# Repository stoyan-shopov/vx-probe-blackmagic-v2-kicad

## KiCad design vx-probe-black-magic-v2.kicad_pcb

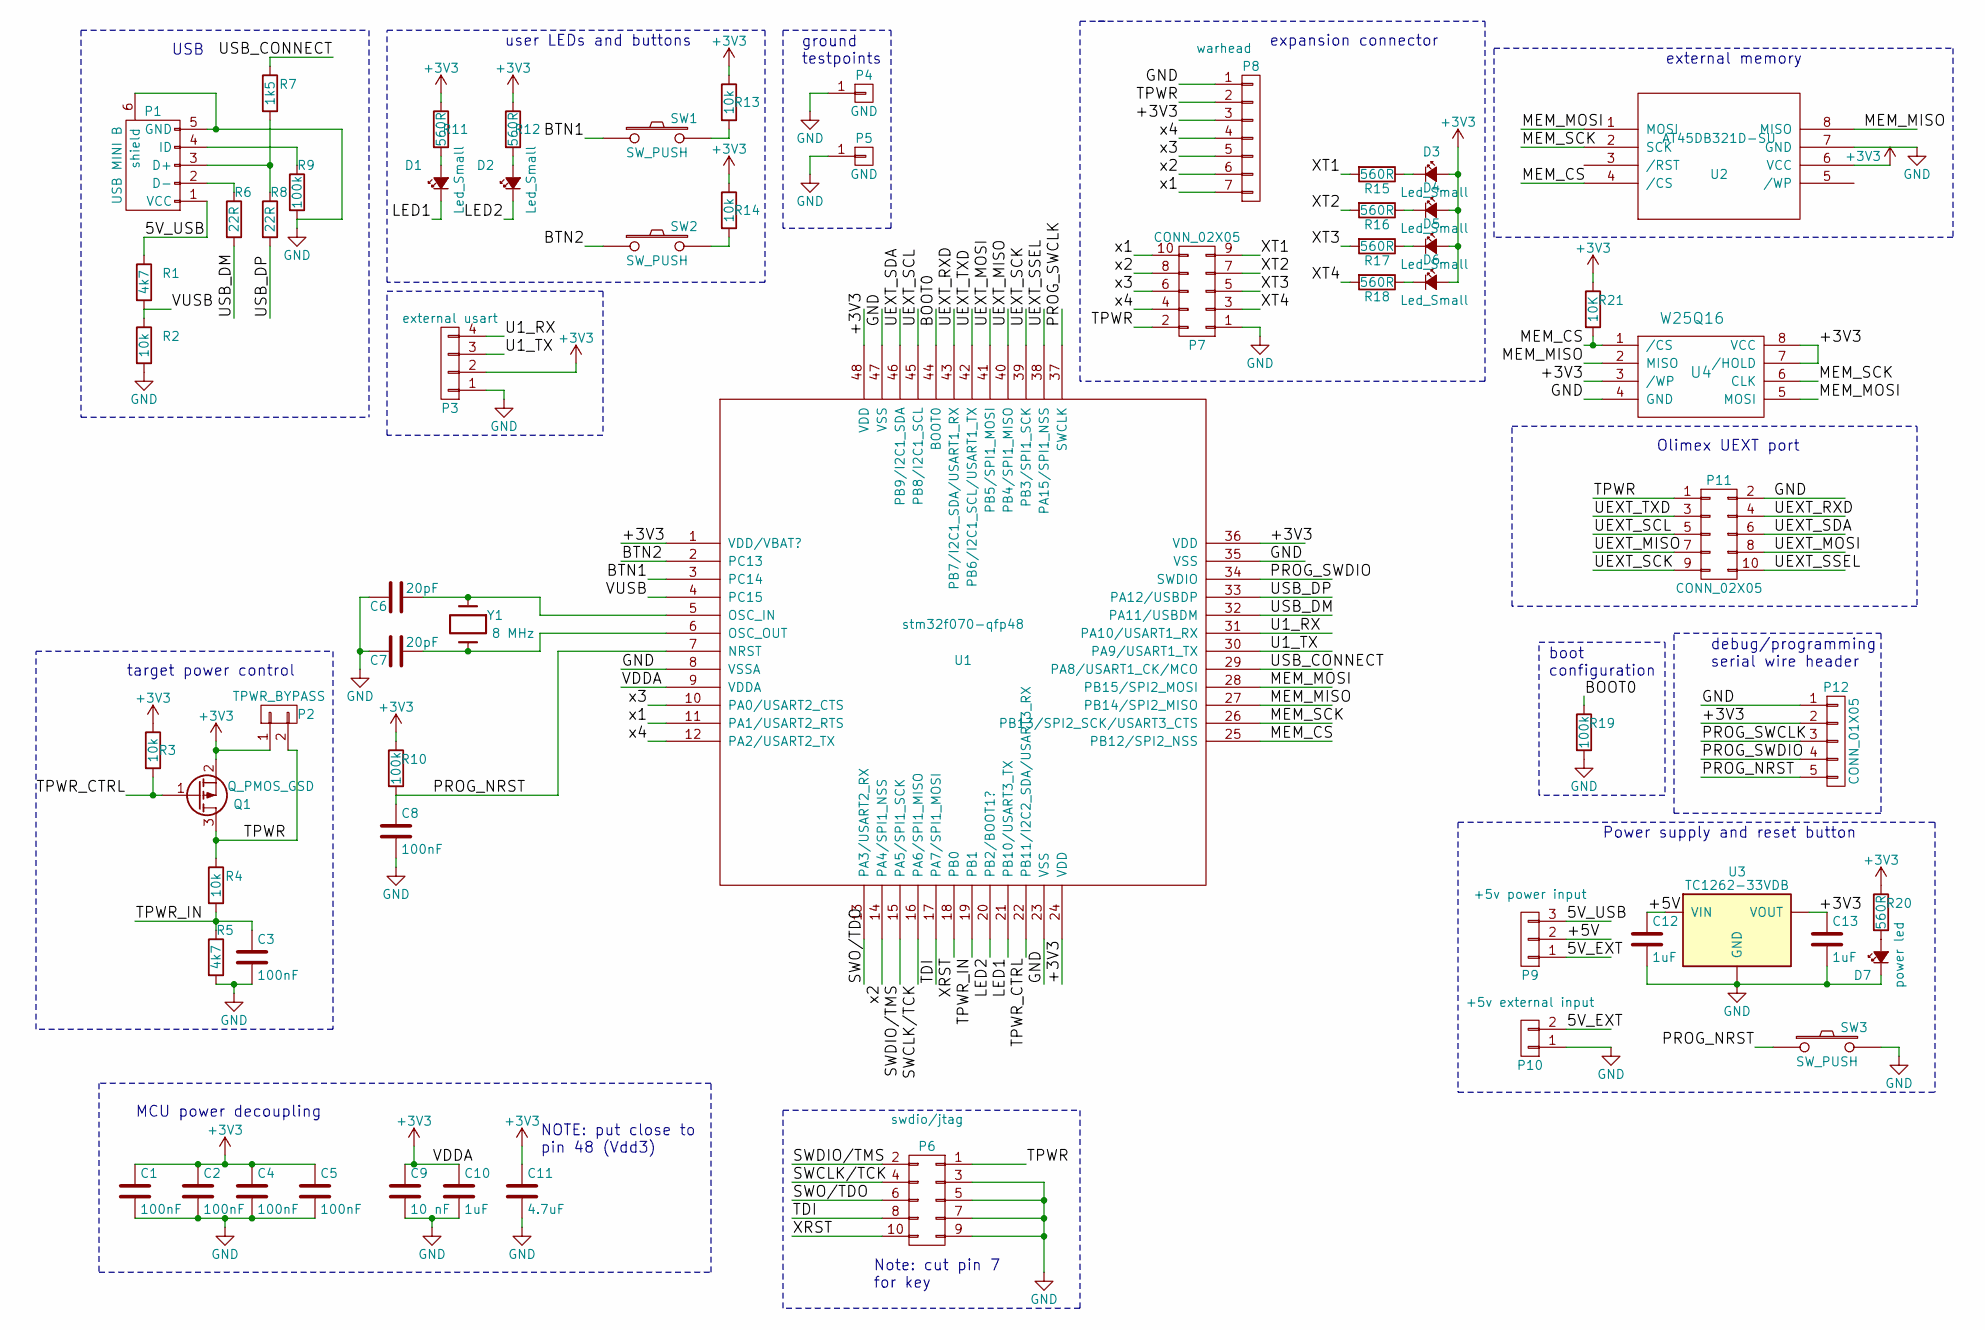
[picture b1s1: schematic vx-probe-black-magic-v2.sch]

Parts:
C1, C2, C3, C4, C5, C8: 100nF; C_0805
C6, C7: 20pF; C_0805
C9: 10 nF; C_0805
C10, C12, C13: 1uF; C_0805
C11: 4.7uF; C_0805
D1, D2, D3, D4, D5, D6: Led_Small; LED_0805
D7: power led; LED_0805
P1: USB MINI B; USB_Mini-B
P2: TPWR_BYPASS; Pin_Header_Straight_1x02
P3: external usart; Pin_Header_Straight_1x04
P4, P5: GND; Pin_Header_Straight_1x01
P6: swdio/jtag; IDC_Header_Straight_10pins
P7: CONN_02X05; Pin_Header_Straight_2x05
P8: warhead; Pin_Header_Straight_1x07
P9: +5v power input; Pin_Header_Straight_1x03
P10: +5v external input; Pin_Header_Straight_1x02
P11: CONN_02X05; IDC_Header_Straight_10pins
P12: CONN_01X05; Pin_Header_Straight_1x05
Q1: Q_PMOS_GSD; SOT-23
R1, R5: 4k7; R_0805
R2, R3, R4, R13, R14: 10k; R_0805
R6, R8: 22R; R_0805
R7: 1k5; R_0805
R9, R10, R19: 100k; R_0805
R11, R12, R15, R16, R17, R18, R20: 560R; R_0805
R21: 10K; R_0805
SW1, SW2, SW3: SW_PUSH; SW_PUSH_6mm
U1: stm32f070-qfp48; LQFP-48_7x7mm_Pitch0.5mm
U2: AT45DB321D-SU; SOIJ-8_5.3x5.3mm_Pitch1.27mm
U3: TC1262-33VDB; SOT-223
U4: W25Q16; SOIJ-8_5.3x5.3mm_Pitch1.27mm
Y1: 8 MHz; Crystal_HC49-U_Vertical

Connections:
+3V3: C1.1, C2.1, C4.1, C5.1, C9.1, C10.1, C11.1, C13.1, D3.2 (A), D4.2 (A), D5.2 (A), D6.2 (A), P2.1, P3.2, P8.3, P12.2, Q1.2 (S), R3.1, R10.1, R11.1, R12.1, R13.1, R14.1, R20.1, R21.1, U1.1 (VDD/VBAT?), U1.9 (VDDA), U1.24 (VDD), U1.36 (VDD), U1.48 (VDD), U2.6 (VCC), U3.3 (VOUT), U4.3 (/WP), U4.7 (/HOLD), U4.8 (VCC)
/5V_EXT: P9.1, P10.2
/5V_USB: P1.1 (VCC), P9.3, R1.1
/+5V: C12.1, P9.2, U3.1 (VIN)
/BOOT0: R19.1, U1.44 (BOOT0)
/BTN1: SW1.1, U1.3 (PC14)
/BTN2: SW2.1, U1.2 (PC13)
/LED1: D1.1 (K), U1.21 (PB10/USART3_TX)
/LED2: D2.1 (K), U1.20 (PB2/BOOT1?)
/MEM_CS: R21.2, U1.25 (PB12/SPI2_NSS), U2.4 (/CS), U4.1 (/CS)
/MEM_MISO: U1.27 (PB14/SPI2_MISO), U2.8 (MISO), U4.2 (MISO)
/MEM_MOSI: U1.28 (PB15/SPI2_MOSI), U2.1 (MOSI), U4.5 (MOSI)
/MEM_SCK: U1.26 (PB13/SPI2_SCK/USART3_CTS), U2.2 (SCK), U4.6 (CLK)
/PROG_NRST: C8.1, P12.5, R10.2, SW3.1, U1.7 (NRST)
/PROG_SWCLK: P12.3, U1.37 (SWCLK)
/PROG_SWDIO: P12.4, U1.34 (SWDIO)
/SWCLK/TCK: P6.4, U1.16 (PA6/SPI1_MISO)
/SWDIO/TMS: P6.2, U1.15 (PA5/SPI1_SCK)
/SWO/TDO: P6.6, U1.13 (PA3/USART2_RX)
/TDI: P6.8, U1.17 (PA7/SPI1_MOSI)
/TPWR: P2.2, P6.1, P7.2, P8.2, P11.1, Q1.3 (D), R4.1
/TPWR_CTRL: Q1.1 (G), R3.2, U1.22 (PB11/I2C2_SDA/USART3_RX)
/TPWR_IN: C3.1, R4.2, R5.1, U1.19 (PB1)
/U1_RX: P3.4, U1.31 (PA10/USART1_RX)
/U1_TX: P3.3, U1.30 (PA9/USART1_TX)
/UEXT_MISO: P11.7, U1.40 (PB4/SPI1_MISO)
/UEXT_MOSI: P11.8, U1.41 (PB5/SPI1_MOSI)
/UEXT_RXD: P11.4, U1.43 (PB7/I2C1_SDA/USART1_RX)
/UEXT_SCK: P11.9, U1.39 (PB3/SPI1_SCK)
/UEXT_SCL: P11.5, U1.45 (PB8/I2C1_SCL)
/UEXT_SDA: P11.6, U1.46 (PB9/I2C1_SDA)
/UEXT_SSEL: P11.10, U1.38 (PA15/SPI1_NSS)
/UEXT_TXD: P11.3, U1.42 (PB6/I2C1_SCL/USART1_TX)
/USB_CONNECT: R7.1, U1.29 (PA8/USART1_CK/MCO)
/USB_DM: R6.2, U1.32 (PA11/USBDM)
/USB_DP: R8.2, U1.33 (PA12/USBDP)
/VUSB: R1.2, R2.1, U1.4 (PC15)
/XRST: P6.10, U1.18 (PB0)
/XT1: P7.9, R15.2
/XT2: P7.7, R16.2
/XT3: P7.5, R17.2
/XT4: P7.3, R18.2
/x1: P7.10, P8.7, U1.11 (PA1/USART2_RTS)
/x2: P7.8, P8.6, U1.14 (PA4/SPI1_NSS)
/x3: P7.6, P8.5, U1.10 (PA0/USART2_CTS)
/x4: P7.4, P8.4, U1.12 (PA2/USART2_TX)
GND: C1.2, C2.2, C3.2, C4.2, C5.2, C6.2, C7.2, C8.2, C9.2, C10.2, C11.2, C12.2, C13.2, D7.1 (K), P1.5 (GND), P1.6 (shield), P3.1, P4.1, P5.1, P6.3, P6.5, P6.7, P6.9, P7.1, P8.1, P10.1, P11.2, P12.1, R2.2, R5.2, R9.2, R19.2, SW3.2, U1.8 (VSSA), U1.23 (VSS), U1.35 (VSS), U1.47 (VSS), U2.7 (GND), U3.2 (GND), U3.4 (GND), U4.4 (GND)
unnamed: C6.1, U1.5 (OSC_IN), Y1.1
unnamed: C7.1, U1.6 (OSC_OUT), Y1.2
unnamed: D1.2 (A), R11.2
unnamed: D2.2 (A), R12.2
unnamed: D3.1 (K), R15.1
unnamed: D4.1 (K), R16.1
unnamed: D5.1 (K), R17.1
unnamed: D6.1 (K), R18.1
unnamed: D7.2 (A), R20.2
unnamed: P1.2 (D-), R6.1
unnamed: P1.3 (D+), R7.2, R8.1
unnamed: P1.4 (ID), R9.1
unnamed: R13.2, SW1.2
unnamed: R14.2, SW2.2

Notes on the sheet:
MCU power decoupling
USB
external memory
Olimex UEXT port
NOTE: put close to pin 48 (Vdd3)
debug/programming serial wire header
boot configuration
Power supply and reset button
Note: cut pin 7 for key
user LEDs and buttons
ground testpoints
expansion connector
target power control

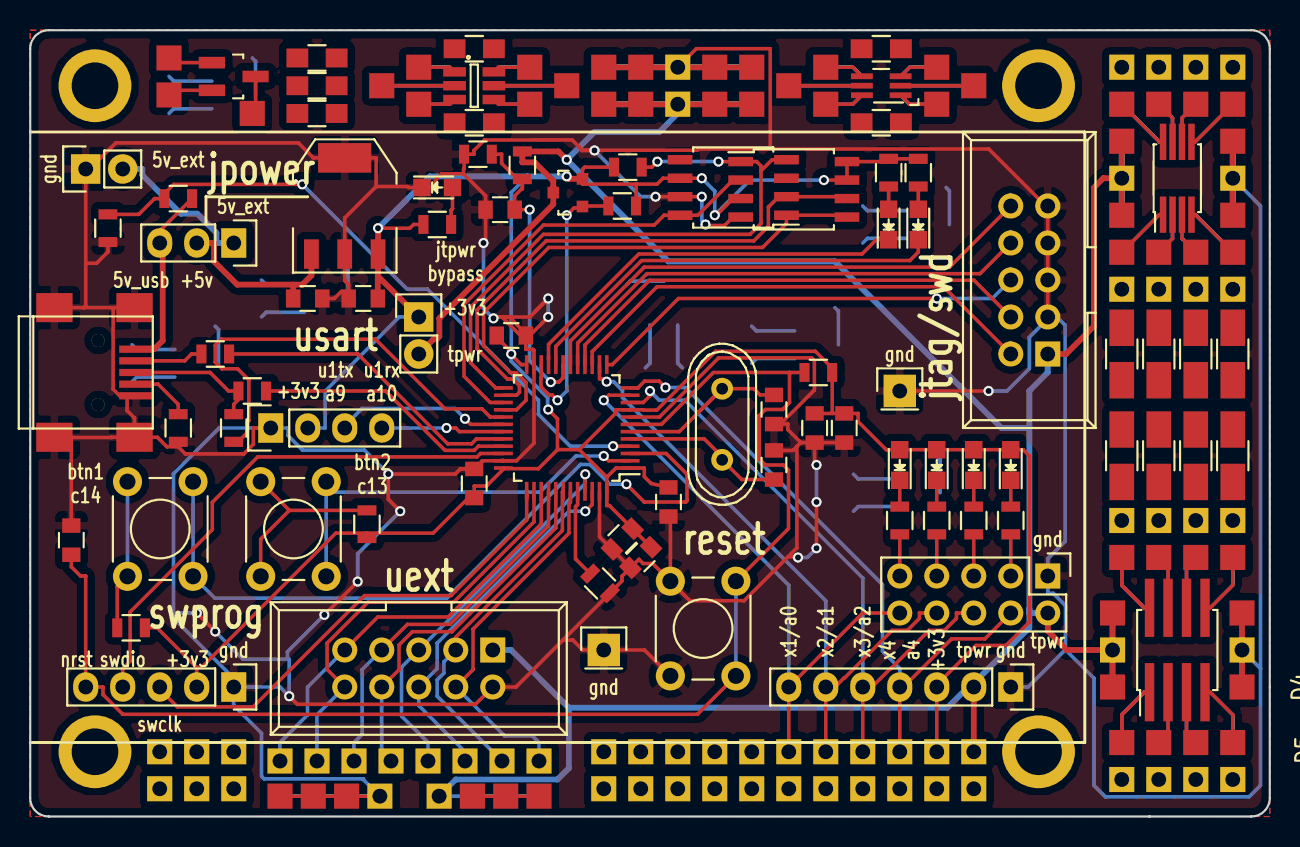
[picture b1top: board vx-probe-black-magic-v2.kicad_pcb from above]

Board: 2 copper layers, 85.1 x 54.0 mm, 62 parts (0 on the bottom side), 61 nets.

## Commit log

2016-09-13 new project created
2016-09-13 datasheet directory added
2016-09-13 stm32f103 part datasheet added
2016-09-13 local library added
2016-09-13 started schematics drawing
2016-09-13 reset circuit added
2016-09-13 started assigning component footprints
2016-09-13 bugfix
2016-09-13 added the mcu power decoupling
2016-09-13 drew the usb connection
2016-09-13 assigned more component footprints
2016-09-13 generated a netlist file
2016-09-13 updated the pcb
2016-09-13 added the at45db32 datasheet
2016-09-13 added the at45db32 library part
2016-09-13 assigned the at45db32 part footprint
2016-09-13 wired up the external spi memory
2016-09-13 wired up the olimex UEXT port
2016-09-13 added the original blackmagic probe schematics for reference
2016-09-13 added missing pull-up resistor on the usb-data-plus line
2016-09-13 added serial wire debug/programming header
2016-09-13 added boot selection setup
2016-09-13 added power supply block
2016-09-13 made capacitor values more readable
2016-09-13 added tc1262 datasheet
2016-09-13 updated components' annotations and footprints
2016-09-13 added missing wires, started placing components
2016-09-13 added locally the 'freerouter' autorouting utility
2016-09-14 adjusted minimum via diametercls
2016-09-14 pcb manufacturer document file added
2016-09-14 started placing and routing the swdio/jtag connector
2016-09-14 routing optimizations
2016-09-14 7 vias
2016-09-14 9 vias
2016-09-14 8 vias
2016-09-15 11 vias
2016-09-15 removed i2c bus pull-up resistors
2016-09-15 stm32f070 breakout board schematics added for reference
2016-09-15 stm nucleo-64 boards user manual added for reference
2016-09-15 reorganized layout, autorouting to 7 vias
2016-09-15 defined board dimensions
2016-09-15 started fitting the components inside the board space, autorouting to 14 vias
2016-09-15 autorouting to 8 vias
2016-09-15 displaced the connectors, autorouting to 8 vias
2016-09-15 adding dummy keep-off areas
2016-09-15 adding dummy keep-off areas, autorouting to 9 vias
2016-09-15 adding dummy keep-off areas, autorouting to 5 vias
2016-09-15 placed unused pins utilization connector, autorouting to 13 vias
2016-09-15 bundled tracks closer to each other
2016-09-15 test-routed unused pins
2016-09-15 bundled the uext signals closer together
2016-09-16 track layout optimizations
2016-09-16 added target power control circuitry
2016-09-16 initial routing of the target power control circuitry
2016-09-16 added and routed the 'vbus' usb power detection signal
2016-09-16 routed an unused pin to the 'unused pins' connector
2016-09-16 reorganized the unused pins connector
2016-09-16 placed and routed the reset button and a serial port
2016-09-16 added a pull-up resistor on the target power enable switch (pmosfet)
2016-09-16 moved the crystal closer to the microcontroller
2016-09-16 changed the jtag and uext connectors to idc headers
2016-09-16 displaced the jtag connector
2016-09-16 bundled the jtag signals closer together
2016-09-16 made the power-to-target tracks thicker
2016-09-17 added a button
2016-09-19 added another button - this adds 4 vias!!!
2016-09-19 rerouted the extension connector
2016-09-19 optimized extension connector routing
2016-09-19 added two led-s
2016-09-19 renamed extension connector signals
2016-09-19 rerouted many pins because of pc13-pc15 output driving limitations
2016-09-19 rerouting, !!! design rules violations present !!!
2016-09-19 rerouting, solved design violations
2016-09-19 routing optimizations - leds still unrouted
2016-09-19 rerouting, moved the vusb resistor divider
2016-09-19 switched two wires on the jtag connector
2016-09-19 rewired the extension connector
2016-09-19 moved the extension port enable connector
2016-09-19 board fully routed
2016-09-19 made the target power supply track thicker
2016-09-19 added a target power-enable bypass jumper
2016-09-19 added a +3v3 wire to the serial port connector
2016-09-19 moved the olimex uext connector
2016-09-19 added a +3v3 wire to the programming connector
2016-09-19 added a ground testpoint
2016-09-19 added ground zone fills
2016-09-19 added unconnected zone fills (copper islands)
2016-09-19 board cleanup
2016-09-19 reannotated the board
2016-09-19 cleaned up the schematic
2016-09-19 reannotated the schematic
2016-09-19 moved the board to the center of the sheet
2016-09-19 tried the new kicad open-gl routing features - shove and others; slight optimizations
2016-09-19 filled zones again
2016-09-20 made power tracks thicker
2016-09-20 performed a 'cleanup tracks and vias' operation in the pcb editor
2016-09-20 moved the reset button
2016-09-20 added the W25Q16 spi memory datasheet for reference
2016-09-20 performed a board cleanup ('cleanup tracks and vias')
2016-09-20 moved component values and references out of the pcb space
2016-09-20 added a footprint for a w25q16 spi memory
2016-09-20 minor track movement
2016-09-20 drew the new board size outline
2016-09-20 placed mounting holes
2016-09-20 fitted the routed board in the new board size space
2016-09-20 adjusted component positions
2016-09-20 started placing pads on the extra board space
2016-09-20 placing pads on the extra board space
2016-09-20 placing pads on the extra board space - put ssop and soic footprints
2016-09-21 cleaned board, started adding standard footprints for prototyping
2016-09-21 edited a prototype footprint
2016-09-21 made a new footprint
2016-09-21 rerouted the expansion jtag wirings
2016-09-21 added a prototyping footprint
2016-09-21 optimized prototyping jtag connector wiring
2016-09-21 added prototyping pads
2016-09-21 modifying prototype design
2016-09-21 optimized jtag connector wiring
2016-09-21 optimized spi memory routing
2016-09-21 moved the mounting holes
2016-09-21 routing the prototype board area
2016-09-21 working on the prototyping board area
2016-09-21 prototyping board area cleanup
2016-09-24 prototyping board area changes
2016-09-26 populated the prototyping board area with component footprints
2016-09-26 added pads to the prototyping board area
2016-09-26 removed extra pads and footprints
2016-09-26 routed the prototyping connectors
2016-09-26 routed power lines to the prototyping board area
2016-09-26 routed some of the prototyping footprints
2016-09-26 fully routed the prototyping board area
2016-09-26 added extra sot23 prototyping footprint clusters
2016-09-26 added filled ground zones
2016-09-26 added a few pads to the prototyping board area
2016-09-26 stiched ground zones with vias
2016-09-26 added copper islands
2016-09-26 renumbered warhead connector pins
2016-09-26 optimized warhead connector wiring
2016-09-26 started adding silkscreen test; routed some power lines on the prototype board area
2016-09-26 adding silkscreen text
2016-09-27 slightly moved a decoupling capacitor
2016-09-27 board finalization for manufacturing
2016-09-27 slightly modified the usb connector footprint; fabrication settings adjustments
2016-09-27 changed via diameters as per fabrication house recommendations
2016-10-06 added fabrication output files
2016-10-07 positioned component values for easy hand-soldering reference
